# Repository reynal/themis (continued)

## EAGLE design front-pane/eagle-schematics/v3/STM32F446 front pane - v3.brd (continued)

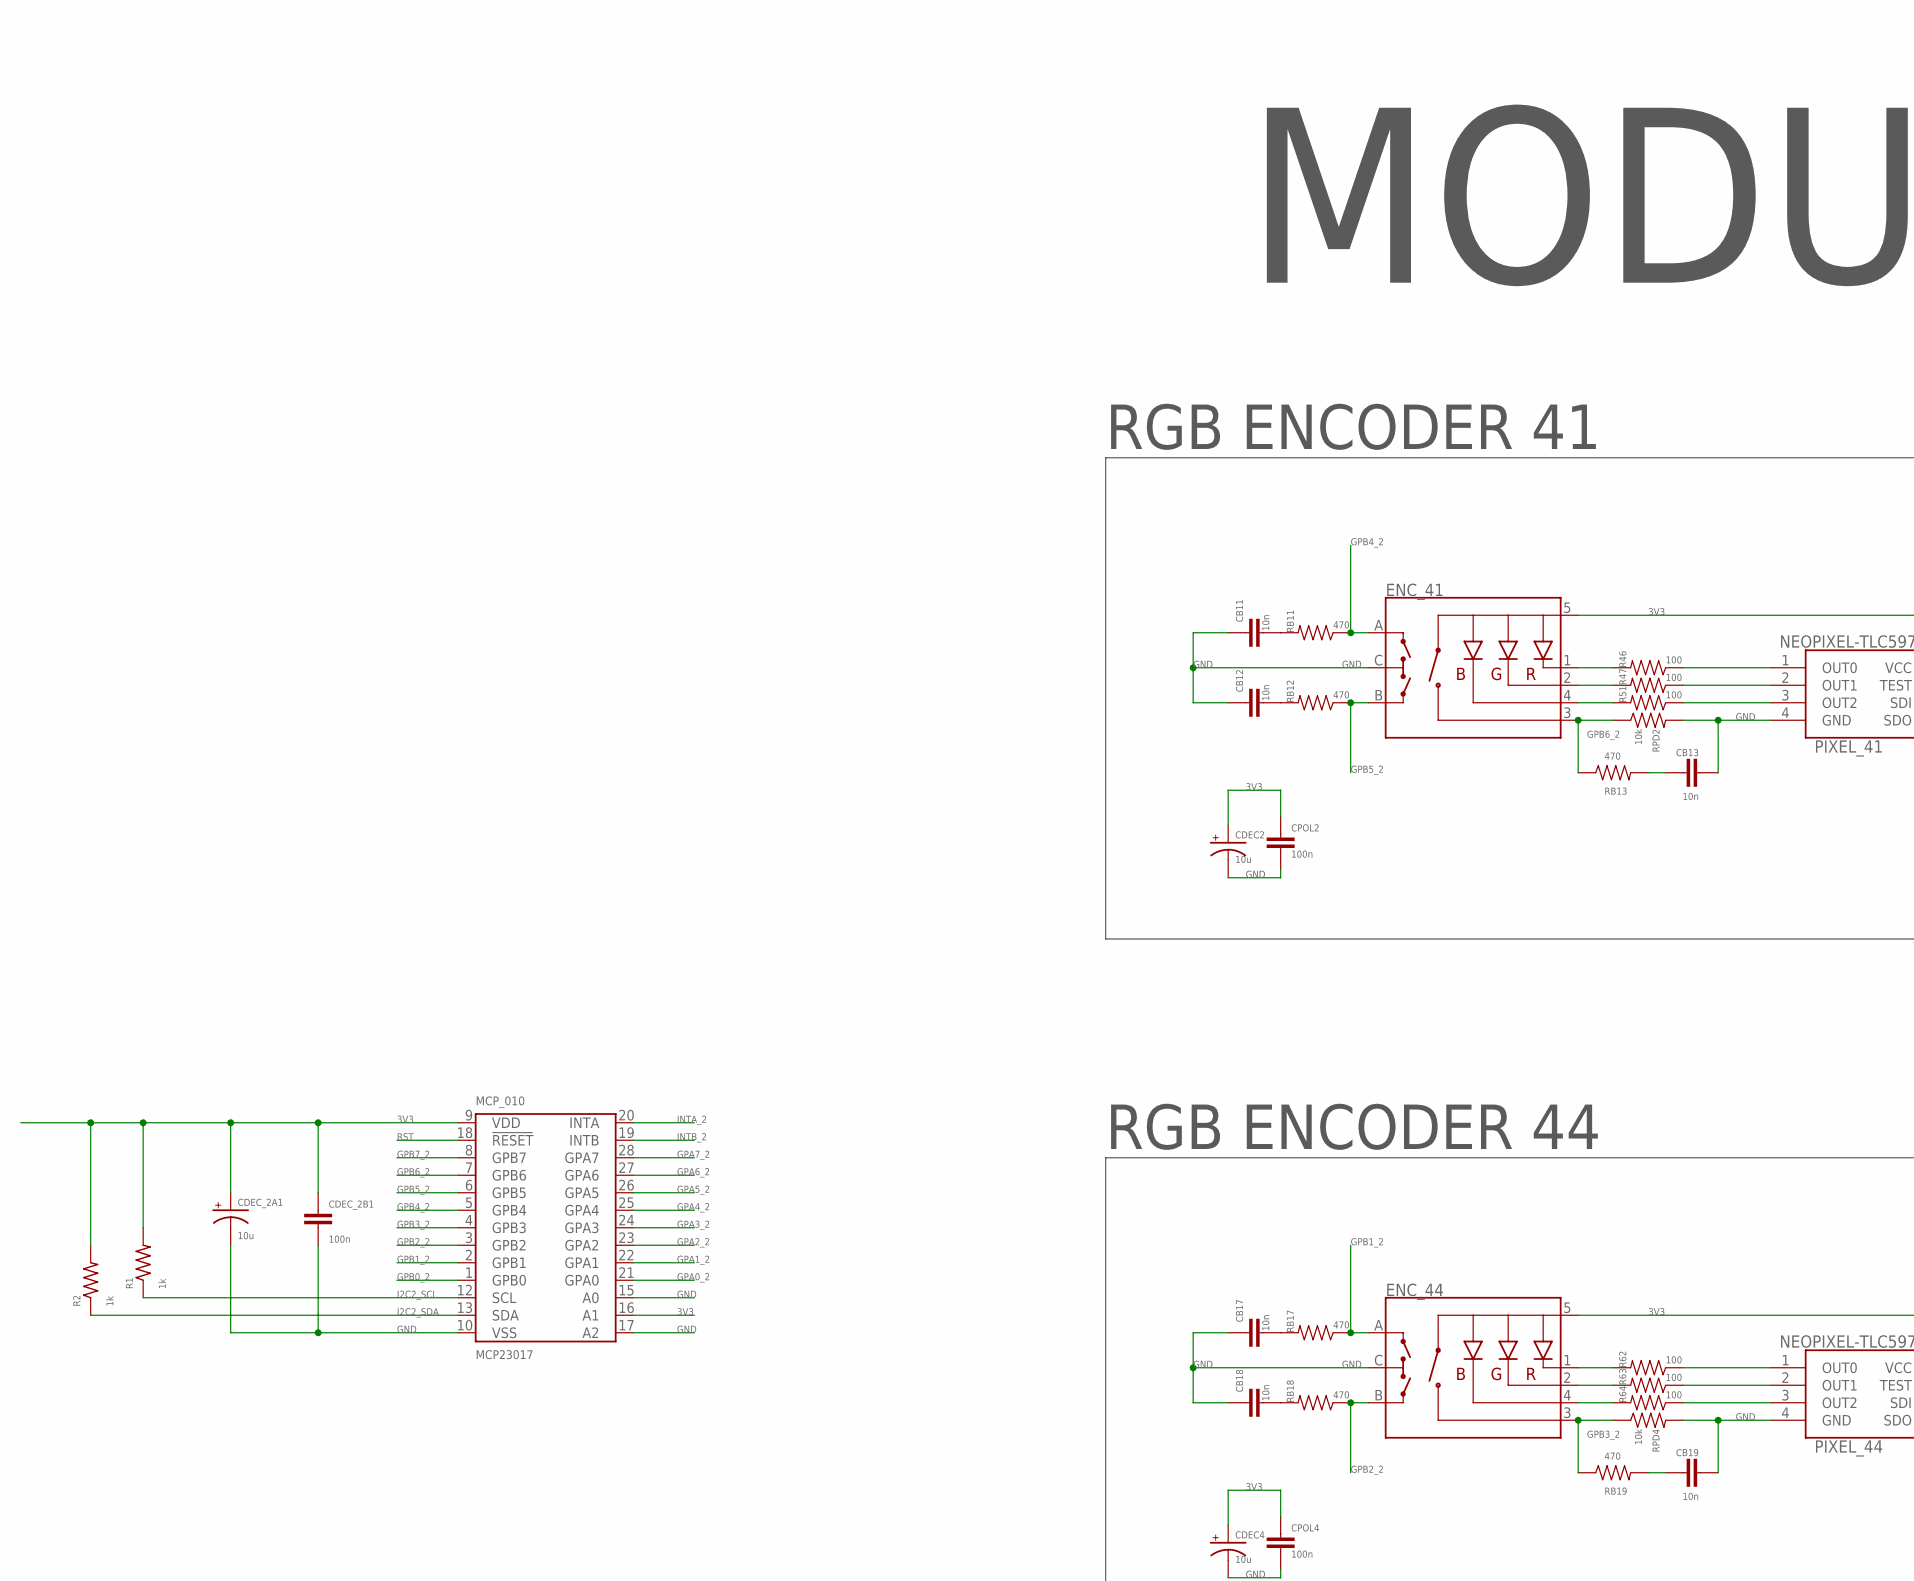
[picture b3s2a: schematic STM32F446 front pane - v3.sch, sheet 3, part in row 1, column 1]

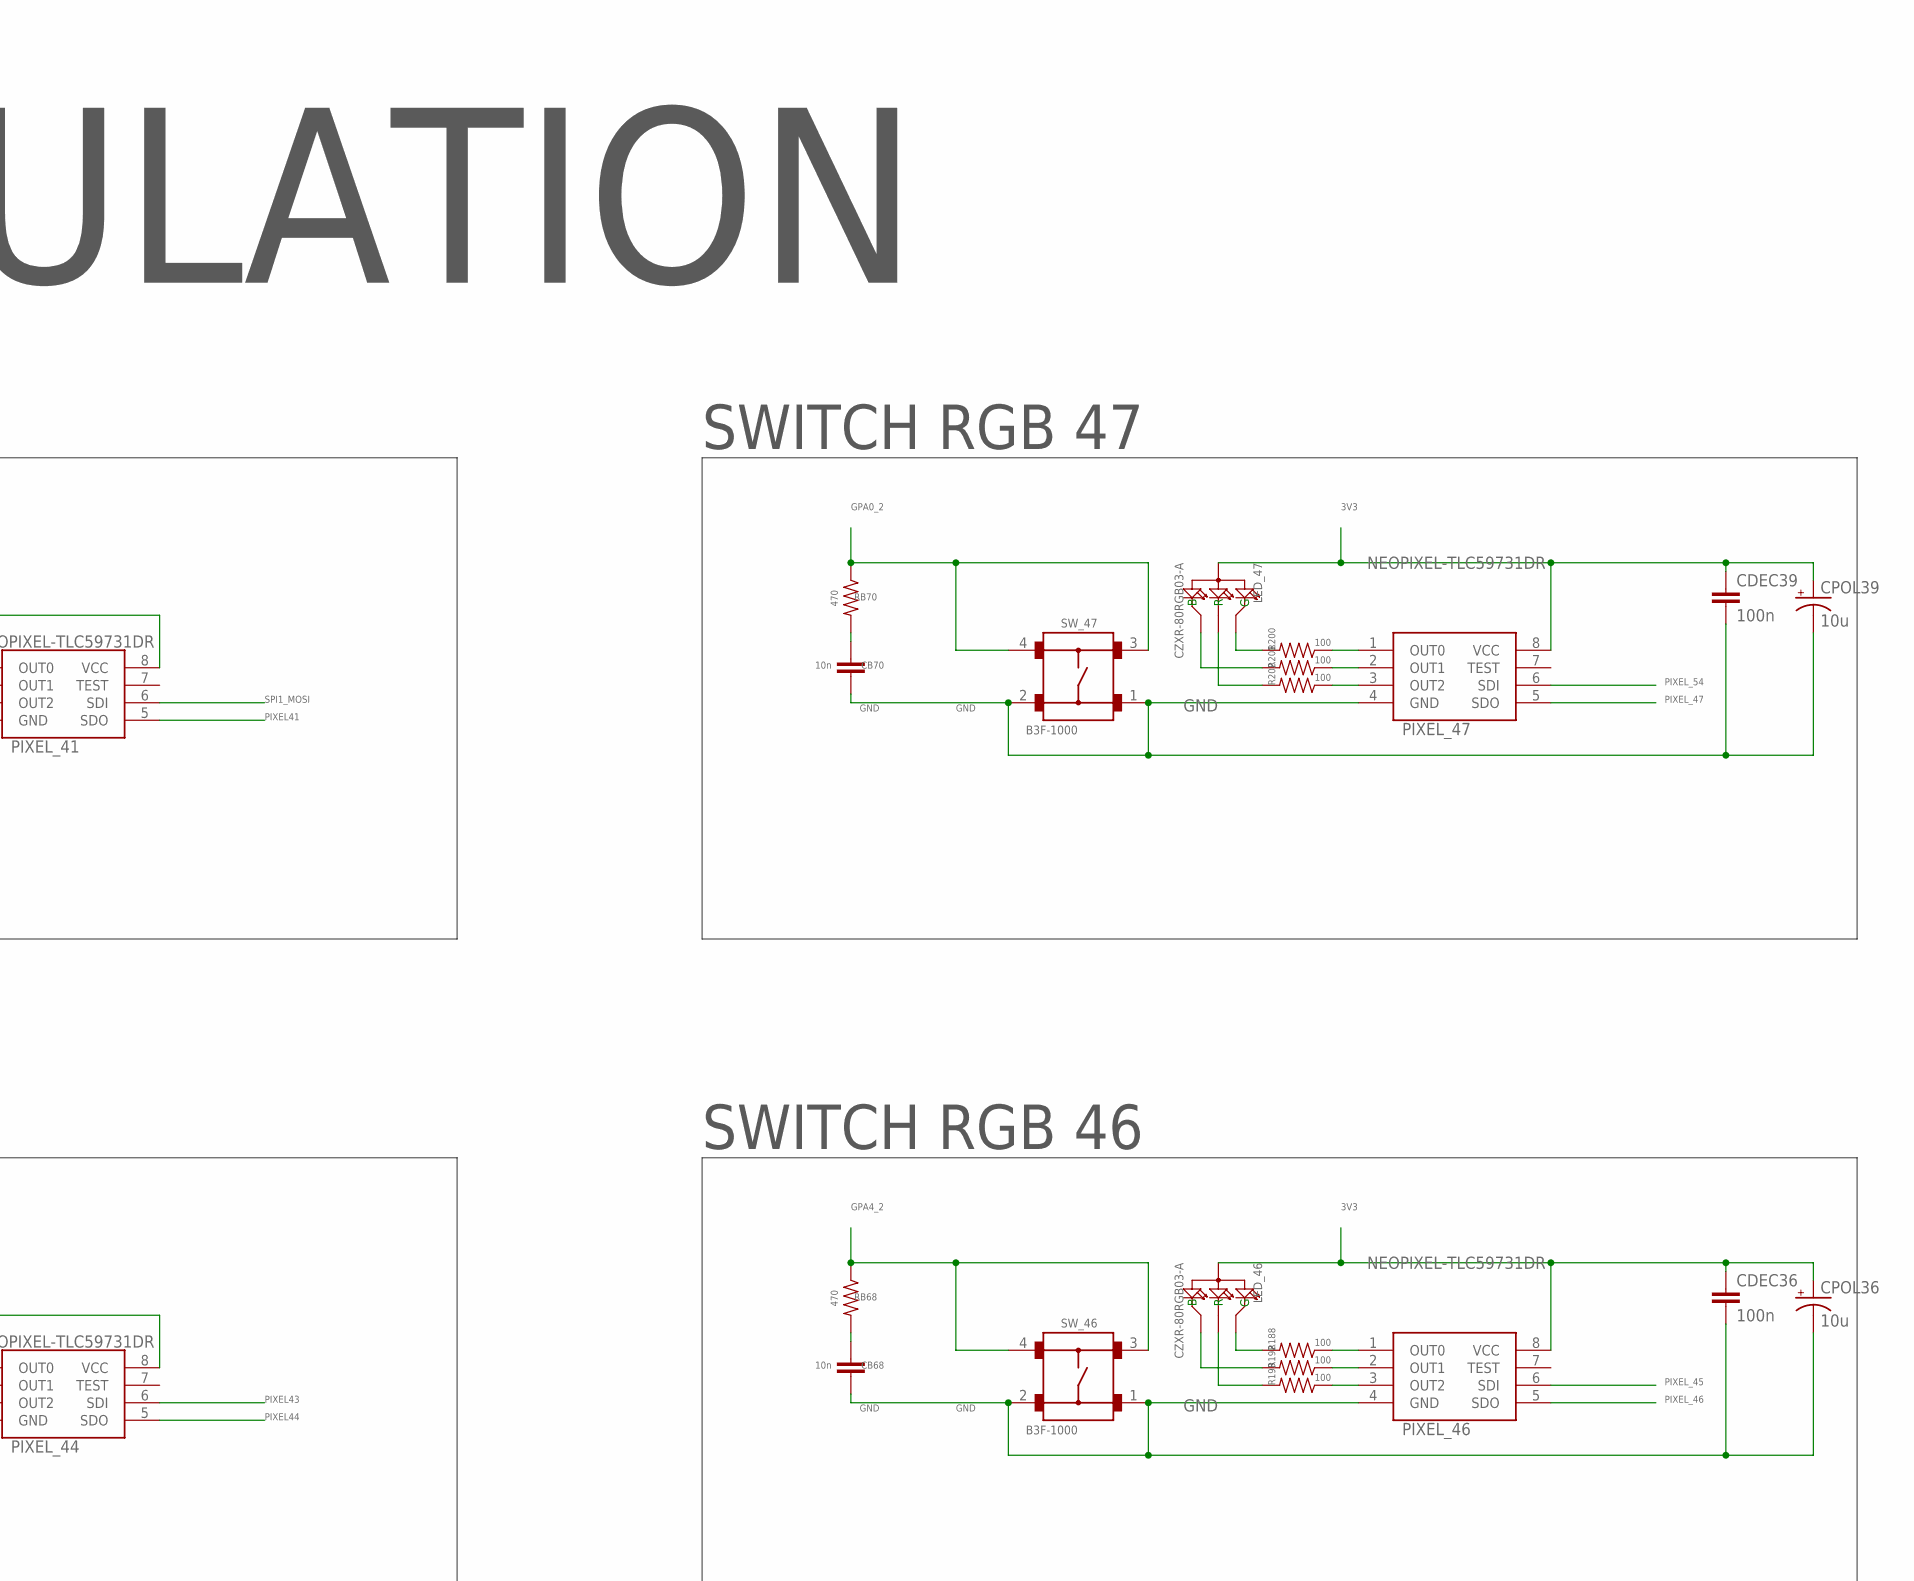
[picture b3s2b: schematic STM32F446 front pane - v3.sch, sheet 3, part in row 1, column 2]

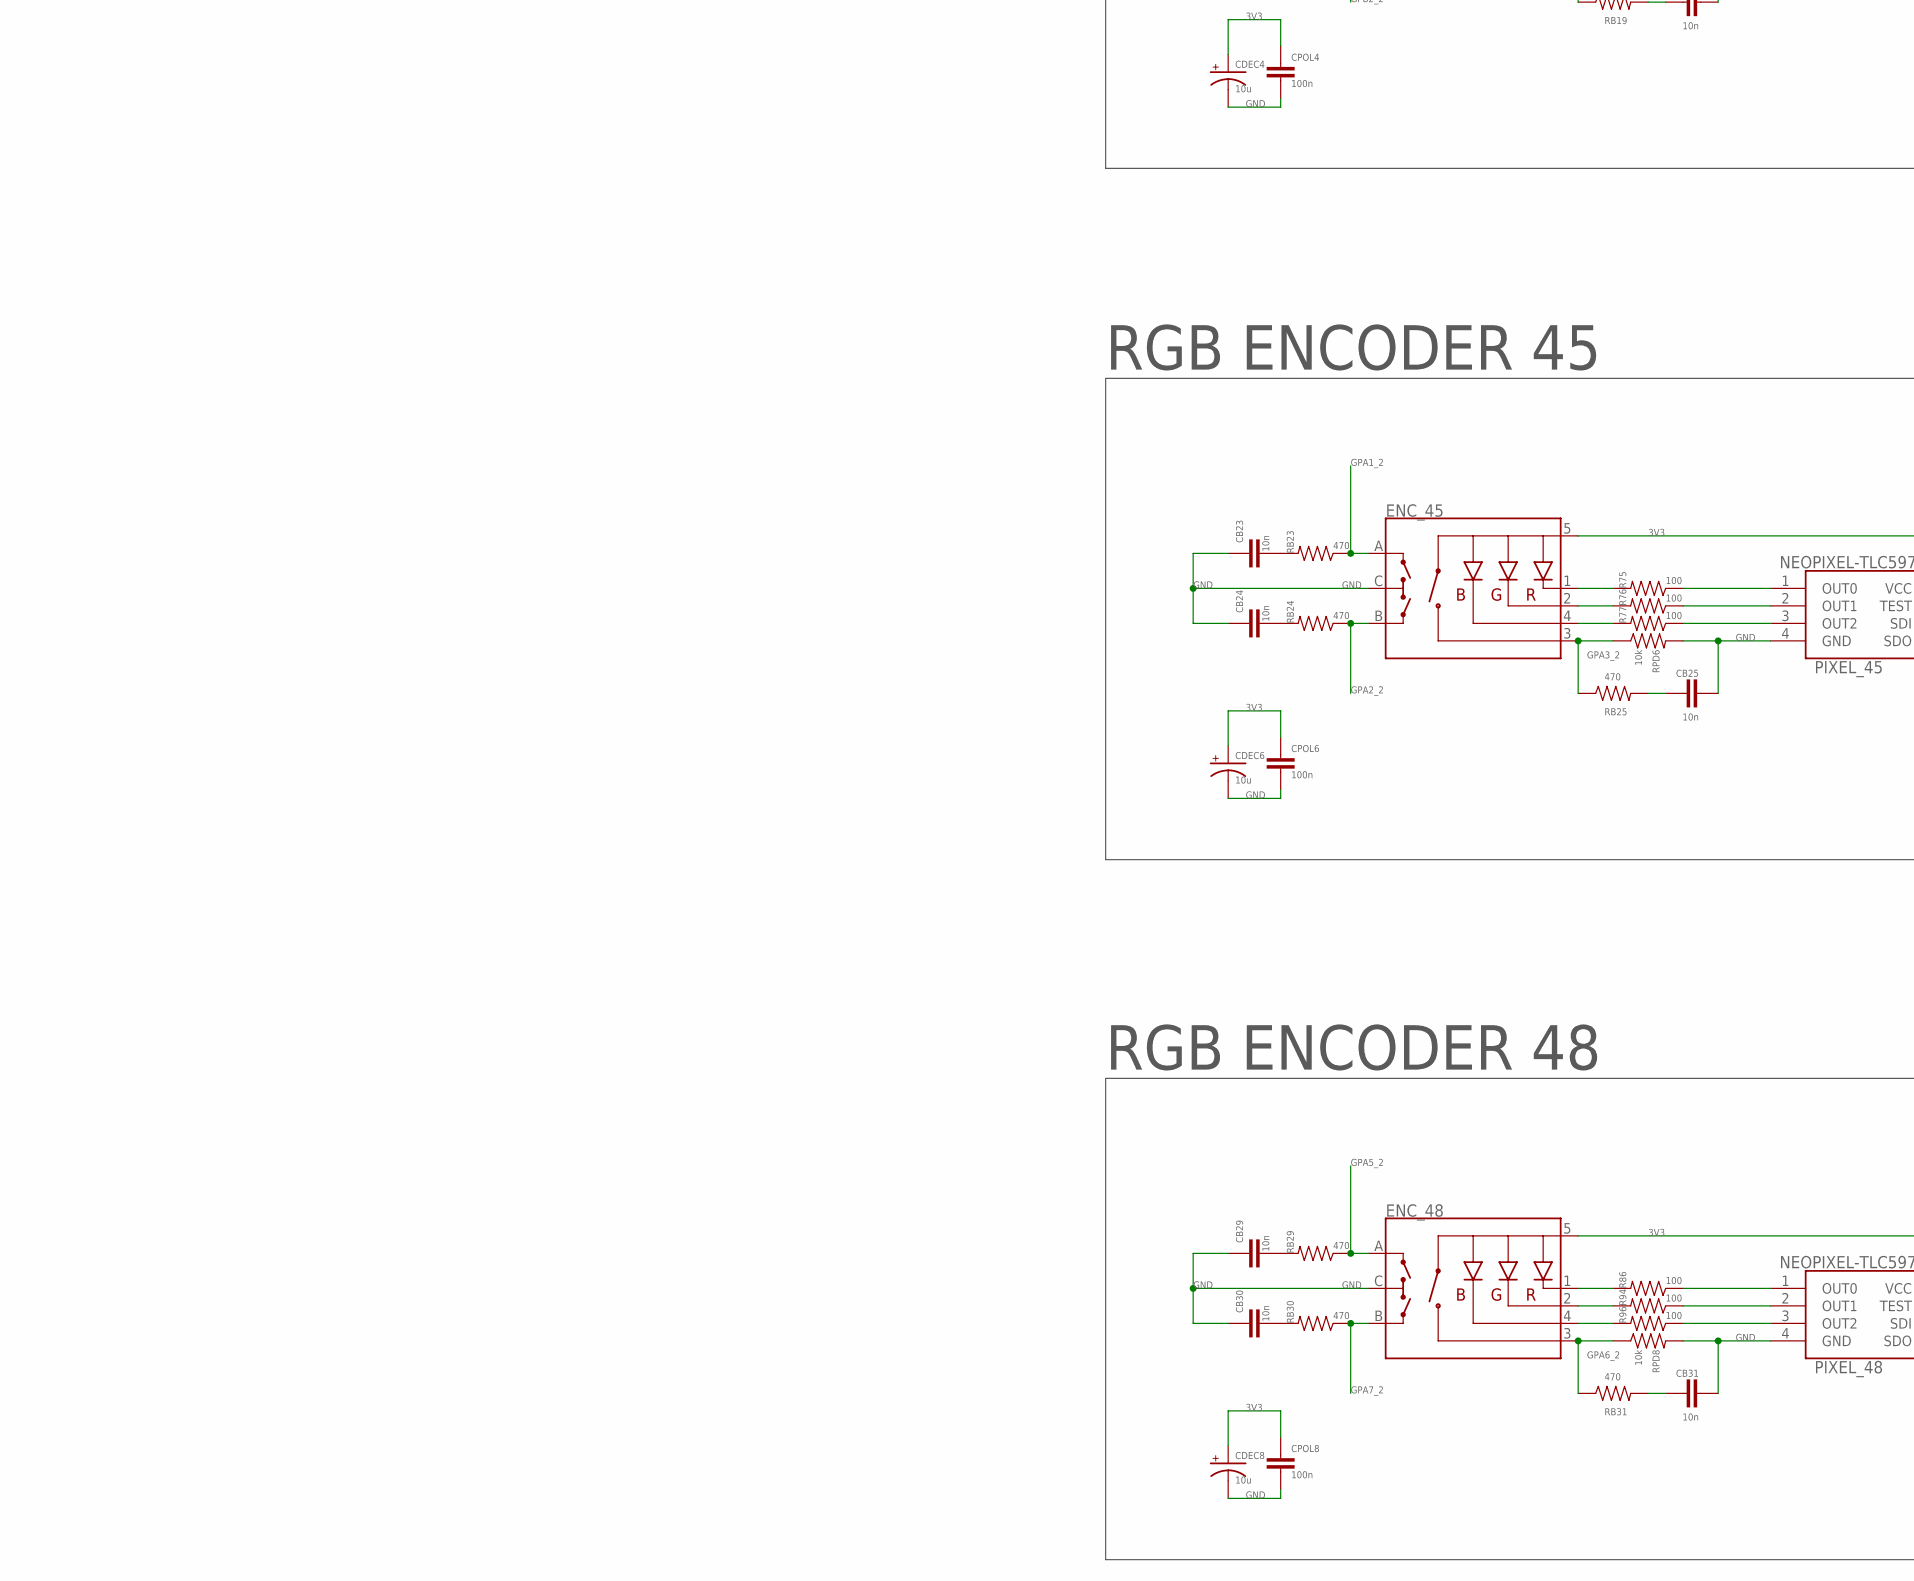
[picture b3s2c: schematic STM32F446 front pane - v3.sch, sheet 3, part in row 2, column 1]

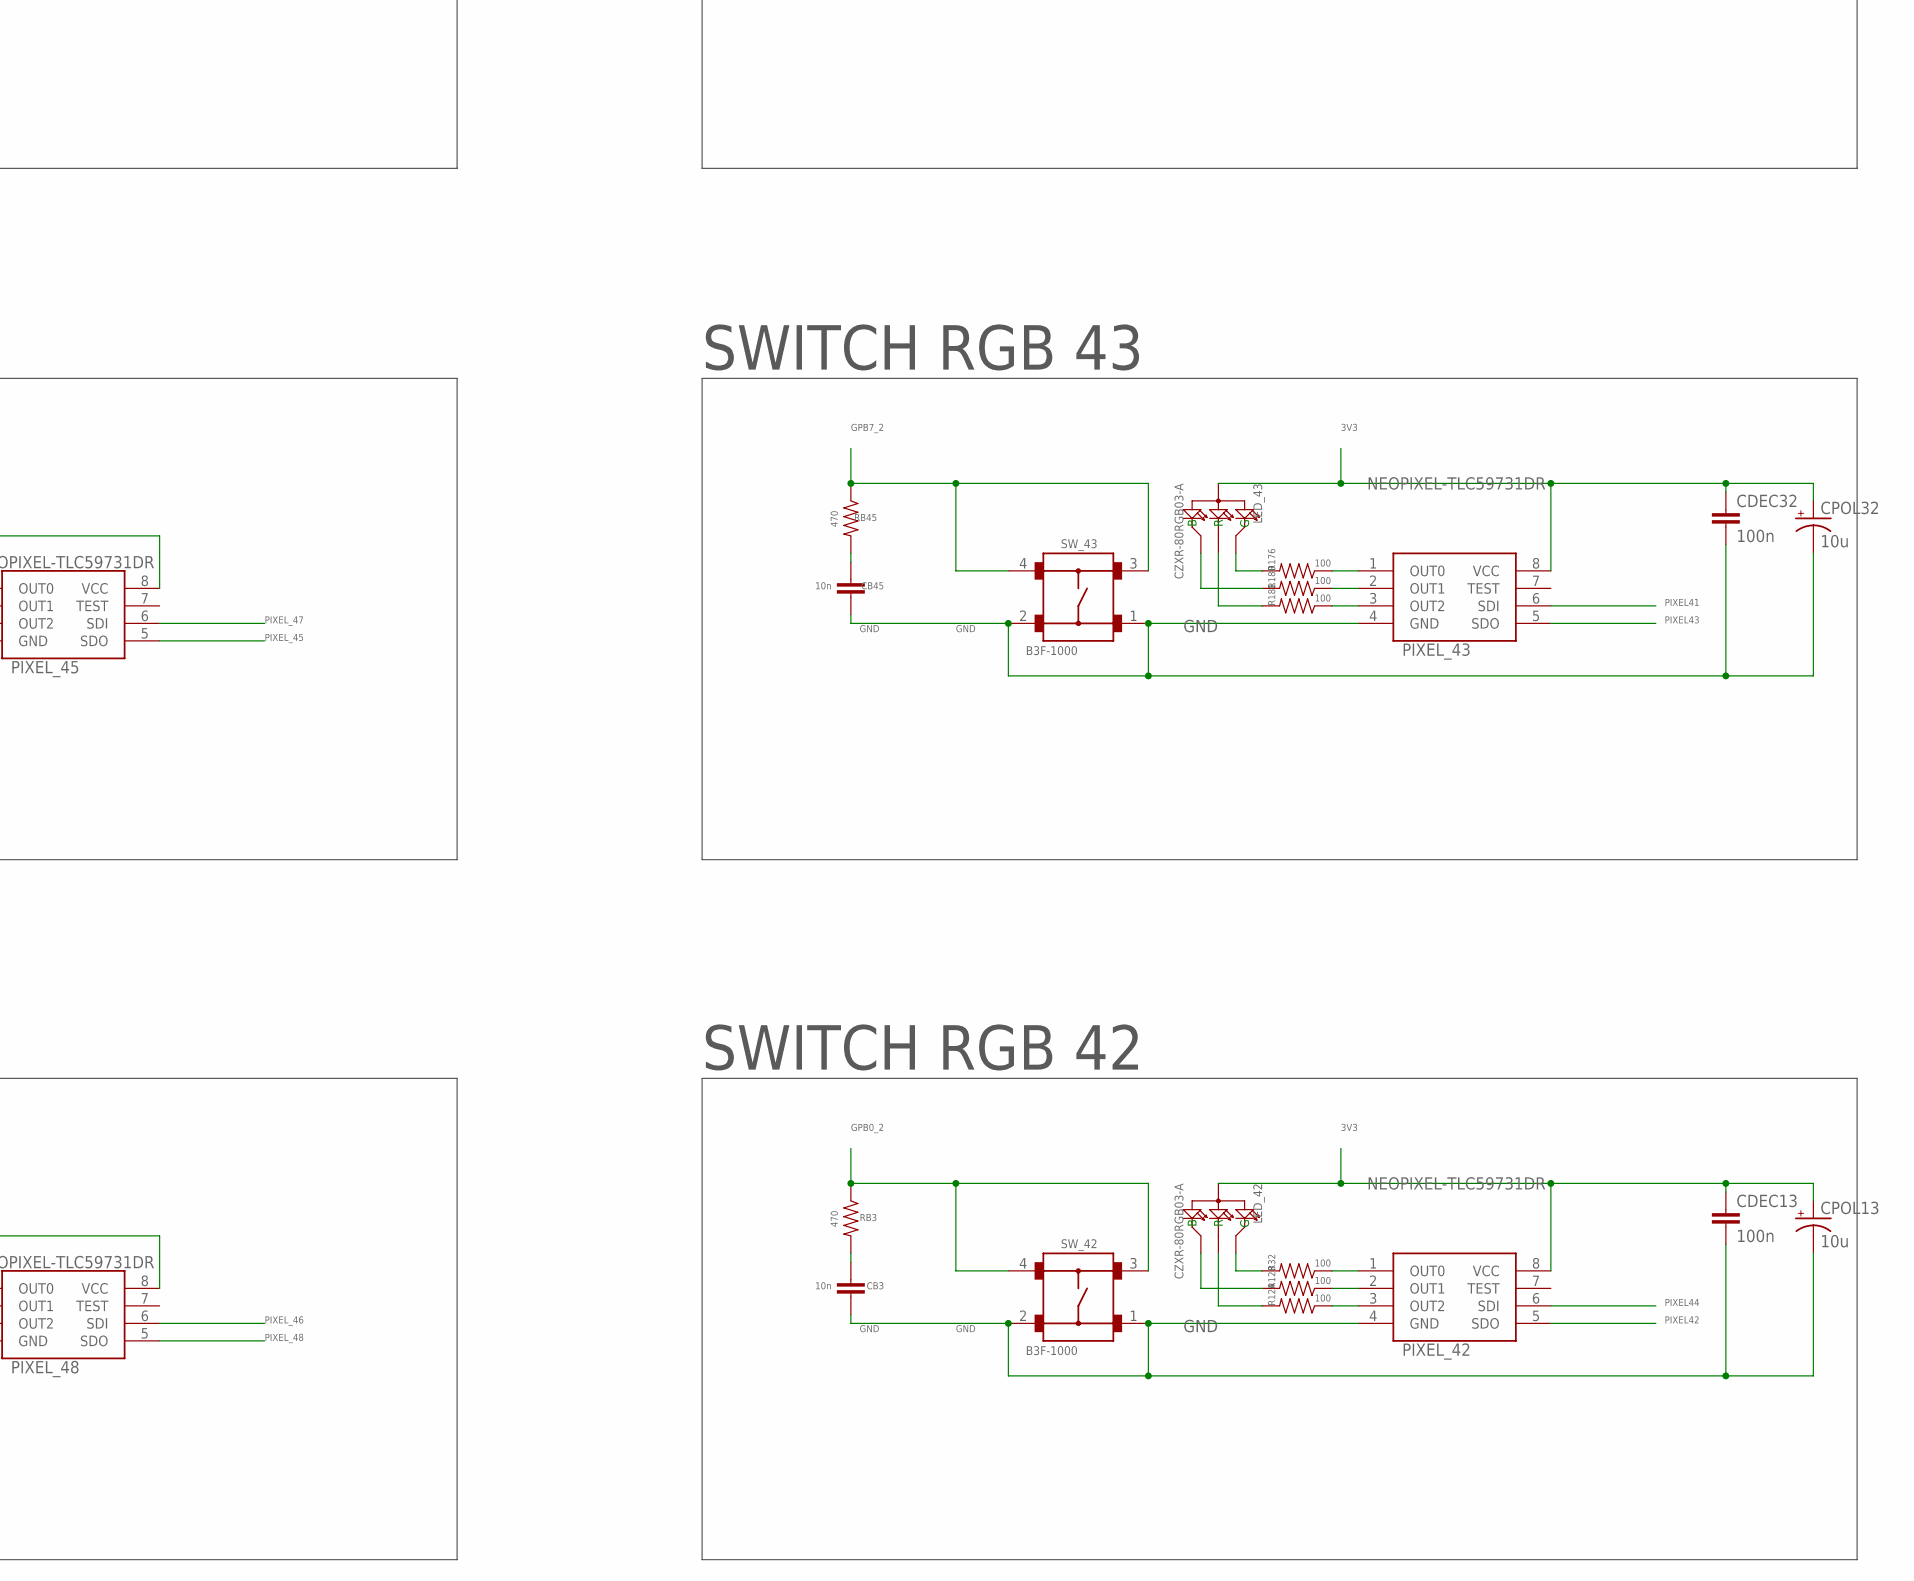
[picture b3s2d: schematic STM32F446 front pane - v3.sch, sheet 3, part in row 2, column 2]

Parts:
CB3, CB11, CB12, CB13, CB17, CB18, CB19, CB23, CB24, CB25, CB29, CB30, CB31, CB45, CB68, CB70: 10n; 0805-CAP
CDEC2, CDEC4, CDEC6, CDEC8: 10u; CPOL2917
CDEC13, CDEC32, CDEC36, CDEC39: 100n; 0805-CAP
CDEC_2A1: 10u; CPOL2917
CDEC_2B1: 100n; 0805-CAP
CPOL2, CPOL4, CPOL6, CPOL8: 100n; 0805-CAP
CPOL13, CPOL32, CPOL36, CPOL39: 10u; CPOL2917
ENC_41, ENC_44, ENC_45, ENC_48: ENCODER-RGB-SWITCH-NO_NUT; ENCODER_LED_3
LED_42, LED_43, LED_46, LED_47: CZXR-80RGB03-A; LED4-2.0-D8.0MM
MCP_010: MCP23017; SOIC-28
PIXEL_41, PIXEL_42, PIXEL_43, PIXEL_44, PIXEL_45, PIXEL_46, PIXEL_47, PIXEL_48: NEOPIXEL-TLC59731DR; SOIC127P600X175-8N
R1, R2: 1k; R0805
R32, R46, R47, R51, R62, R63, R64, R75, R76, R77, R86, R94, R96, R123, R124, R176, R180, R181, R188, R192, R193, R200, R201, R202: 100; 1206
RB3, RB11, RB12, RB13, RB17, RB18, RB19, RB23, RB24, RB25, RB29, RB30, RB31, RB45, RB68, RB70: 470; 1206
RPD2, RPD4, RPD6, RPD8: 10k; 1206
SW_42, SW_43, SW_46, SW_47: B3F-1000

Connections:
3V3: CDEC2.+, CDEC4.+, CDEC6.+, CDEC8.+, CDEC13.1, CDEC32.1, CDEC36.1, CDEC39.1, CDEC_2A1.+, CDEC_2B1.1, CPOL2.1, CPOL4.1, CPOL6.1, CPOL8.1, CPOL13.+, CPOL32.+, CPOL36.+, CPOL39.+, ENC_41.5 (+), ENC_44.5 (+), ENC_45.5 (+), ENC_48.5 (+), LED_42.2 (+), LED_43.2 (+), LED_46.2 (+), LED_47.2 (+), MCP_010.9 (VDD), MCP_010.16 (A1), PIXEL_41.8 (VCC), PIXEL_42.8 (VCC), PIXEL_43.8 (VCC), PIXEL_44.8 (VCC), PIXEL_45.8 (VCC), PIXEL_46.8 (VCC), PIXEL_47.8 (VCC), PIXEL_48.8 (VCC), R1.2, R2.2; also elsewhere on the board
GND: CB3.1, CB11.1, CB12.1, CB13.2, CB17.1, CB18.1, CB19.2, CB23.1, CB24.1, CB25.2, CB29.1, CB30.1, CB31.2, CB45.1, CB68.1, CB70.1, CDEC2.-, CDEC4.-, CDEC6.-, CDEC8.-, CDEC13.2, CDEC32.2, CDEC36.2, CDEC39.2, CDEC_2A1.-, CDEC_2B1.2, CPOL2.2, CPOL4.2, CPOL6.2, CPOL8.2, CPOL13.-, CPOL32.-, CPOL36.-, CPOL39.-, ENC_41.C, ENC_44.C, ENC_45.C, ENC_48.C, MCP_010.10 (VSS), MCP_010.15 (A0), MCP_010.17 (A2), PIXEL_41.4 (GND), PIXEL_42.4 (GND), PIXEL_43.4 (GND), PIXEL_44.4 (GND), PIXEL_45.4 (GND), PIXEL_46.4 (GND), PIXEL_47.4 (GND), PIXEL_48.4 (GND), RPD2.2, RPD4.2, RPD6.2, RPD8.2, SW_42.1, SW_42.2, SW_43.1, SW_43.2, SW_46.1, SW_46.2, SW_47.1, SW_47.2; also elsewhere on the board
GPA0_2: MCP_010.21 (GPA0), RB70.1, SW_47.3, SW_47.4
GPA1_2: ENC_45.A, MCP_010.22 (GPA1), RB23.1
GPA2_2: ENC_45.B, MCP_010.23 (GPA2), RB24.1
GPA3_2: ENC_45.3 (SW), MCP_010.24 (GPA3), RB25.1, RPD6.1
GPA4_2: MCP_010.25 (GPA4), RB68.1, SW_46.3, SW_46.4
GPA5_2: ENC_48.A, MCP_010.26 (GPA5), RB29.1
GPA6_2: ENC_48.3 (SW), MCP_010.27 (GPA6), RB31.1, RPD8.1
GPA7_2: ENC_48.B, MCP_010.28 (GPA7), RB30.1
GPB0_2: MCP_010.1 (GPB0), RB3.1, SW_42.3, SW_42.4
GPB1_2: ENC_44.A, MCP_010.2 (GPB1), RB17.1
GPB2_2: ENC_44.B, MCP_010.3 (GPB2), RB18.1
GPB3_2: ENC_44.3 (SW), MCP_010.4 (GPB3), RB19.1, RPD4.1
GPB4_2: ENC_41.A, MCP_010.5 (GPB4), RB11.1
GPB5_2: ENC_41.B, MCP_010.6 (GPB5), RB12.1
GPB6_2: ENC_41.3 (SW), MCP_010.7 (GPB6), RB13.1, RPD2.1
GPB7_2: MCP_010.8 (GPB7), RB45.1, SW_43.3, SW_43.4
I2C2_SCL: MCP_010.12 (SCL), R1.1; also elsewhere on the board
I2C2_SDA: MCP_010.13 (SDA), R2.1; also elsewhere on the board
INTA_2: MCP_010.20 (INTA); also elsewhere on the board
INTB_2: MCP_010.19 (INTB); also elsewhere on the board
unnamed: PIXEL_42.1 (OUT0), R32.1
unnamed: PIXEL_42.2 (OUT1), R123.1
unnamed: ENC_41.1 (-R), R46.2
unnamed: ENC_41.2 (-G), R47.2
unnamed: ENC_41.4 (-B), R51.2
unnamed: PIXEL_41.1 (OUT0), R46.1
unnamed: PIXEL_41.2 (OUT1), R47.1
unnamed: PIXEL_41.3 (OUT2), R51.1
unnamed: CB11.2, RB11.2
unnamed: CB12.2, RB12.2
unnamed: CB13.1, RB13.2
unnamed: ENC_44.1 (-R), R62.2
unnamed: ENC_44.2 (-G), R63.2
unnamed: ENC_44.4 (-B), R64.2
unnamed: PIXEL_44.1 (OUT0), R62.1
unnamed: PIXEL_44.2 (OUT1), R63.1
unnamed: PIXEL_44.3 (OUT2), R64.1
unnamed: CB17.2, RB17.2
unnamed: CB18.2, RB18.2
unnamed: CB19.1, RB19.2
unnamed: ENC_45.1 (-R), R75.2
unnamed: ENC_45.2 (-G), R76.2
unnamed: ENC_45.4 (-B), R77.2
unnamed: PIXEL_45.1 (OUT0), R75.1
unnamed: PIXEL_45.2 (OUT1), R76.1
unnamed: PIXEL_45.3 (OUT2), R77.1
unnamed: CB23.2, RB23.2
unnamed: CB24.2, RB24.2
unnamed: CB25.1, RB25.2
unnamed: ENC_48.1 (-R), R86.2
unnamed: ENC_48.2 (-G), R94.2
unnamed: ENC_48.4 (-B), R96.2
unnamed: PIXEL_48.1 (OUT0), R86.1
unnamed: PIXEL_48.2 (OUT1), R94.1
unnamed: PIXEL_48.3 (OUT2), R96.1
unnamed: CB29.2, RB29.2
unnamed: CB30.2, RB30.2
unnamed: CB31.1, RB31.2
unnamed: PIXEL_42.3 (OUT2), R124.1
unnamed: CB3.2, RB3.2
unnamed: LED_42.1 (R), R124.2
unnamed: LED_42.4 (B), R123.2
unnamed: LED_42.3 (G), R32.2
unnamed: PIXEL_43.1 (OUT0), R176.1
unnamed: PIXEL_43.2 (OUT1), R180.1
unnamed: PIXEL_43.3 (OUT2), R181.1
unnamed: CB45.2, RB45.2
unnamed: LED_43.1 (R), R181.2
unnamed: LED_43.4 (B), R180.2
unnamed: LED_43.3 (G), R176.2
unnamed: PIXEL_46.1 (OUT0), R188.1
unnamed: PIXEL_46.2 (OUT1), R192.1
unnamed: PIXEL_46.3 (OUT2), R193.1
unnamed: CB68.2, RB68.2
unnamed: LED_46.1 (R), R193.2
unnamed: LED_46.4 (B), R192.2
unnamed: LED_46.3 (G), R188.2
unnamed: PIXEL_47.1 (OUT0), R200.1
unnamed: PIXEL_47.2 (OUT1), R201.1
unnamed: PIXEL_47.3 (OUT2), R202.1
unnamed: CB70.2, RB70.2
unnamed: LED_47.1 (R), R202.2
unnamed: LED_47.4 (B), R201.2
unnamed: LED_47.3 (G), R200.2
PIXEL41: PIXEL_41.5 (SDO), PIXEL_43.6 (SDI)
PIXEL42: PIXEL_42.5 (SDO); also elsewhere on the board
PIXEL43: PIXEL_43.5 (SDO), PIXEL_44.6 (SDI)
PIXEL44: PIXEL_42.6 (SDI), PIXEL_44.5 (SDO)
PIXEL_45: PIXEL_45.5 (SDO), PIXEL_46.6 (SDI)
PIXEL_46: PIXEL_46.5 (SDO), PIXEL_48.6 (SDI)
PIXEL_47: PIXEL_45.6 (SDI), PIXEL_47.5 (SDO)
PIXEL_48: PIXEL_48.5 (SDO); also elsewhere on the board
PIXEL_54: PIXEL_47.6 (SDI); also elsewhere on the board
RST: MCP_010.18 (!RESET); also elsewhere on the board
SPI1_MOSI: PIXEL_41.6 (SDI); also elsewhere on the board

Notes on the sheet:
MODULATION
RGB ENCODER 41
RGB ENCODER 44
RGB ENCODER 45
RGB ENCODER 48
SWITCH RGB 42
SWITCH RGB 43
SWITCH RGB 46
SWITCH RGB 47
